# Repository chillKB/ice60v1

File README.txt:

This is my first ever PCB design. It is tested and working, but I was still learning and it definitely does not follow best practices.

Check out my GitHub profile for more recent designs since I love making PCBs, especially 60% ones.

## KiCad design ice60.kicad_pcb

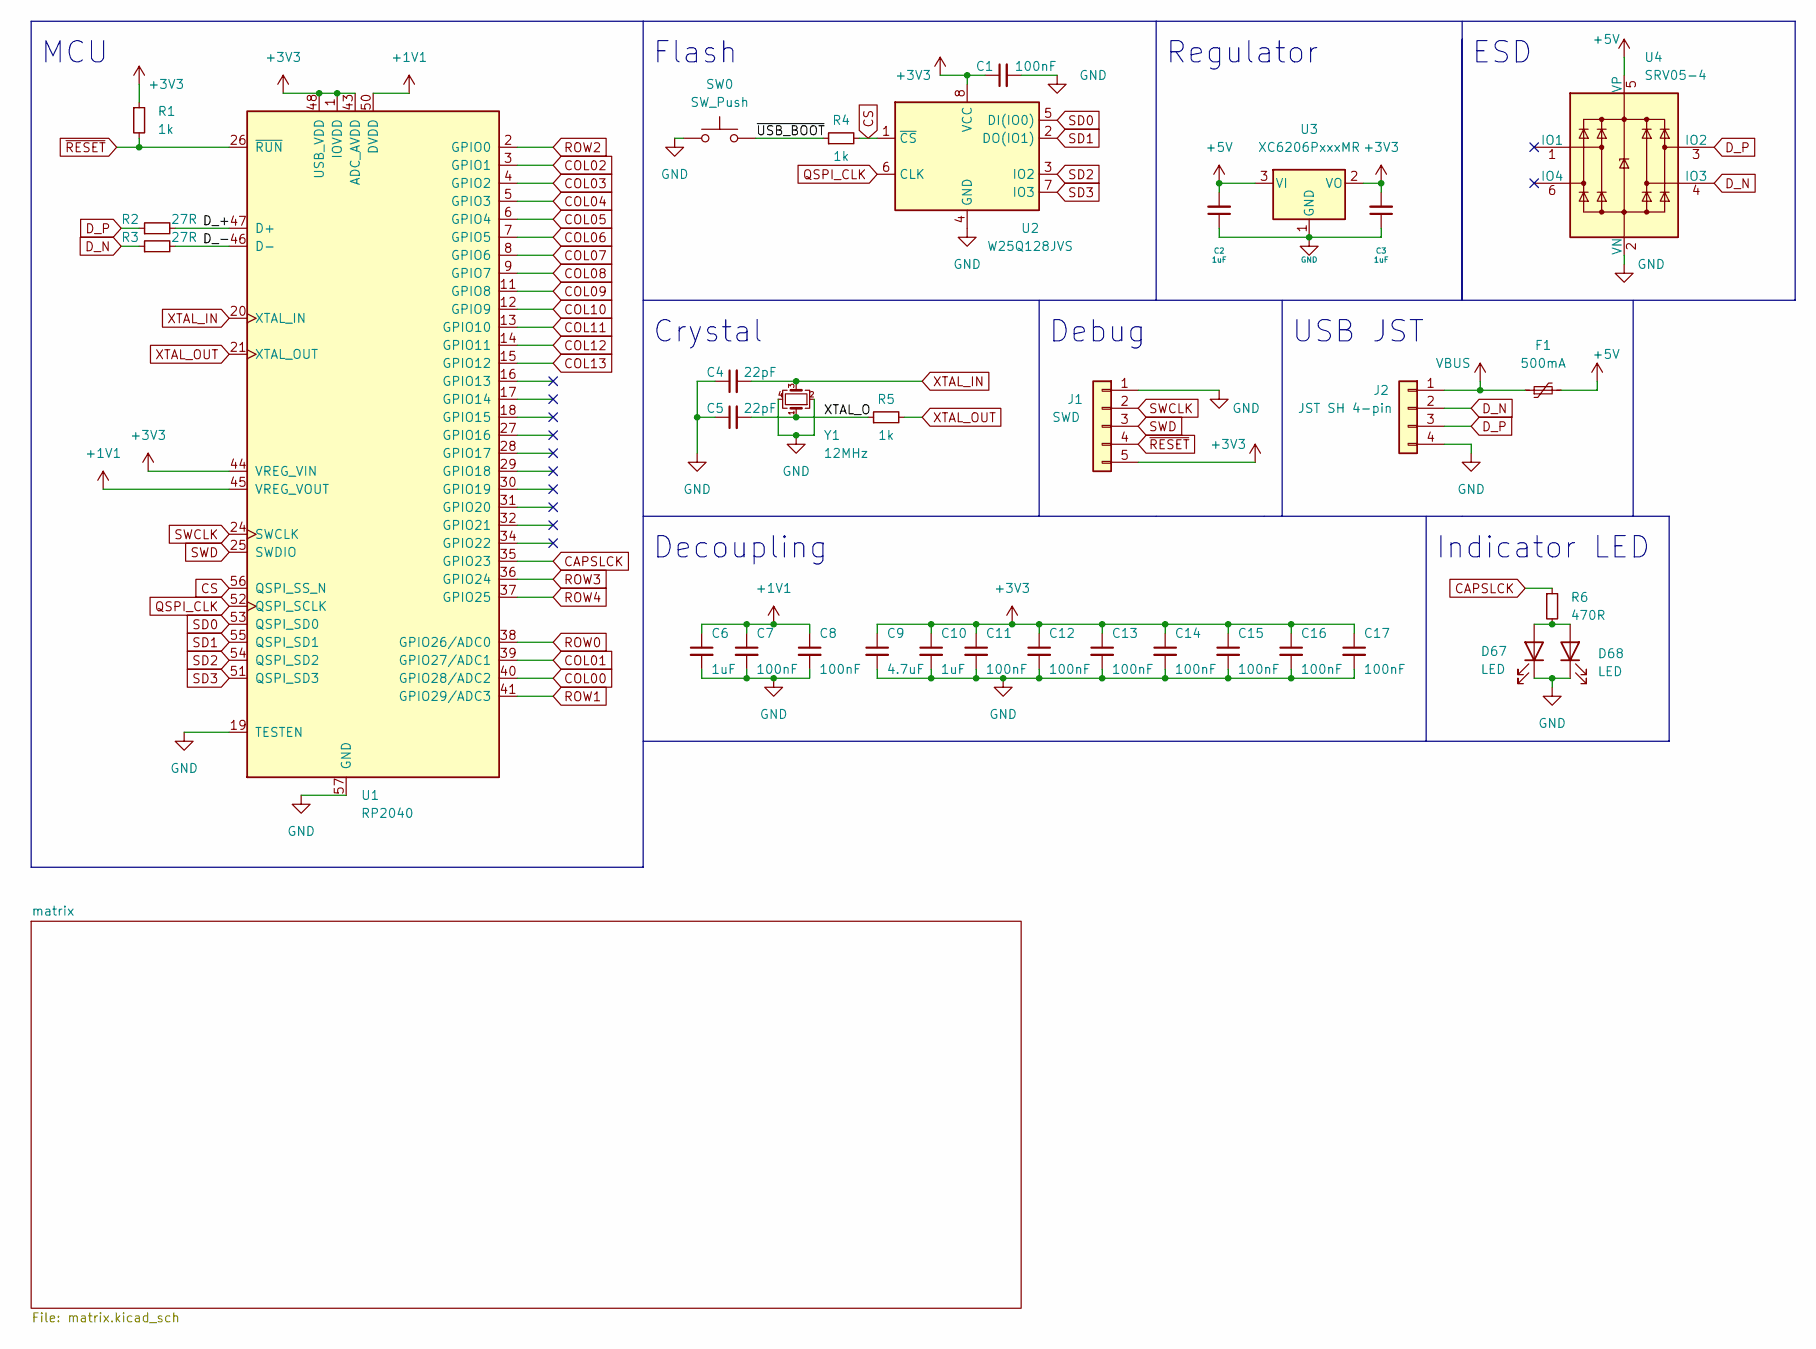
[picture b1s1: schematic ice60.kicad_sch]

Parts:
C1, C7, C8, C11, C12, C13, C14, C15, C16, C17: 100nF; C_0402_1005Metric; LCSC C1525
C2, C3, C6, C10: 1uF; C_0402_1005Metric; LCSC C52923
C4, C5: 22pF; C_0402_1005Metric; LCSC C1555
C9: 4.7uF; C_0402_1005Metric; LCSC C15525
D67: LED; LED_MX_3mm
D68: LED; LED_MX_3mm-FLIPPED
F1: 500mA; Fuse_1206_3216Metric; LCSC C135342
J1: SWD; PinSocket_1x05_P2.54mm_Vertical
J2: JST SH 4-pin; JST_SH_SM04B-SRSS-TB_1x04-1MP_P1.00mm_Horizontal; LCSC C160404
R1, R4, R5: 1k; R_0402_1005Metric; LCSC C11702
R2, R3: 27R; R_0603_1608Metric; LCSC C25190
R6: 470R; R_0402_1005Metric; LCSC C25117
SW0: SW_Push; PinSocket_1x02_P2.54mm_Vertical
U1: RP2040; RP2040-QFN-56; LCSC C2040
U2: W25Q128JVS; SOIC-8_5.23x5.23mm_P1.27mm; LCSC C131025
U3: XC6206PxxxMR; SOT-23; LCSC C5446
U4: SRV05-4; SOT-23-6-routable; LCSC C85364
Y1: 12MHz; Crystal_SMD_3225-4Pin_3.2x2.5mm; LCSC C9002

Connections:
+1V1: C6.1, C7.1, C8.1, U1.23 (DVDD), U1.45 (VREG_VOUT), U1.50 (DVDD)
+3V3: C1.1, C3.2, C9.1, C10.1, C11.1, C12.1, C13.1, C14.1, C15.1, C16.1, C17.1, J1.5, R1.1, U1.1 (IOVDD), U1.10 (IOVDD), U1.22 (IOVDD), U1.33 (IOVDD), U1.42 (IOVDD), U1.43 (ADC_AVDD), U1.44 (VREG_VIN), U1.48 (USB_VDD), U1.49 (IOVDD), U2.8 (VCC), U3.2 (VO)
+5V: C2.2, F1.2, U3.3 (VI), U4.5 (VP)
/D_+: R2.2, U1.47 (D+)
/D_-: R3.2, U1.46 (D-)
/XTAL_O: C5.2, R5.1, Y1.1
/~USB_BOOT: R4.1, SW0.2
CAPSLCK: R6.1, U1.35 (GPIO23)
COL00: U1.40 (GPIO28/ADC2); also elsewhere on the board
COL01: U1.39 (GPIO27/ADC1); also elsewhere on the board
COL02: U1.3 (GPIO1); also elsewhere on the board
COL03: U1.4 (GPIO2); also elsewhere on the board
COL04: U1.5 (GPIO3); also elsewhere on the board
COL05: U1.6 (GPIO4); also elsewhere on the board
COL06: U1.7 (GPIO5); also elsewhere on the board
COL07: U1.8 (GPIO6); also elsewhere on the board
COL08: U1.9 (GPIO7); also elsewhere on the board
COL09: U1.11 (GPIO8); also elsewhere on the board
COL10: U1.12 (GPIO9); also elsewhere on the board
COL11: U1.13 (GPIO10); also elsewhere on the board
COL12: U1.14 (GPIO11); also elsewhere on the board
COL13: U1.15 (GPIO12); also elsewhere on the board
CS: R4.2, U1.56 (QSPI_SS_N), U2.1 (~CS)
D_N: J2.2, R3.1, U4.4 (IO3)
D_P: J2.3, R2.1, U4.3 (IO2)
GND: C1.2, C2.1, C3.1, C4.1, C5.1, C6.2, C7.2, C8.2, C9.2, C10.2, C11.2, C12.2, C13.2, C14.2, C15.2, C16.2, C17.2, D67.1 (K), D68.1 (K), J1.1, J2.4, SW0.1, U1.19 (TESTEN), U1.57 (GND), U2.4 (GND), U3.1 (GND), U4.2 (VN), Y1.2, Y1.4
unnamed: D67.2 (A), D68.2 (A), R6.2
QSPI_CLK: U1.52 (QSPI_SCLK), U2.6 (CLK)
ROW0: U1.38 (GPIO26/ADC0); also elsewhere on the board
ROW1: U1.41 (GPIO29/ADC3); also elsewhere on the board
ROW2: U1.2 (GPIO0); also elsewhere on the board
ROW3: U1.36 (GPIO24); also elsewhere on the board
ROW4: U1.37 (GPIO25); also elsewhere on the board
SD0: U1.53 (QSPI_SD0), U2.5 (DI(IO0))
SD1: U1.55 (QSPI_SD1), U2.2 (DO(IO1))
SD2: U1.54 (QSPI_SD2), U2.3 (IO2)
SD3: U1.51 (QSPI_SD3), U2.7 (IO3)
SWCLK: J1.2, U1.24 (SWCLK)
SWD: J1.3, U1.25 (SWDIO)
VBUS: F1.1, J2.1
XTAL_IN: C4.2, U1.20 (XTAL_IN), Y1.3
XTAL_OUT: R5.2, U1.21 (XTAL_OUT)
~RESET: J1.4, R1.2, U1.26 (~RUN)

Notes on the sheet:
Crystal
Indicator LED
USB JST
Regulator
ESD
MCU
Debug
Flash
Decoupling

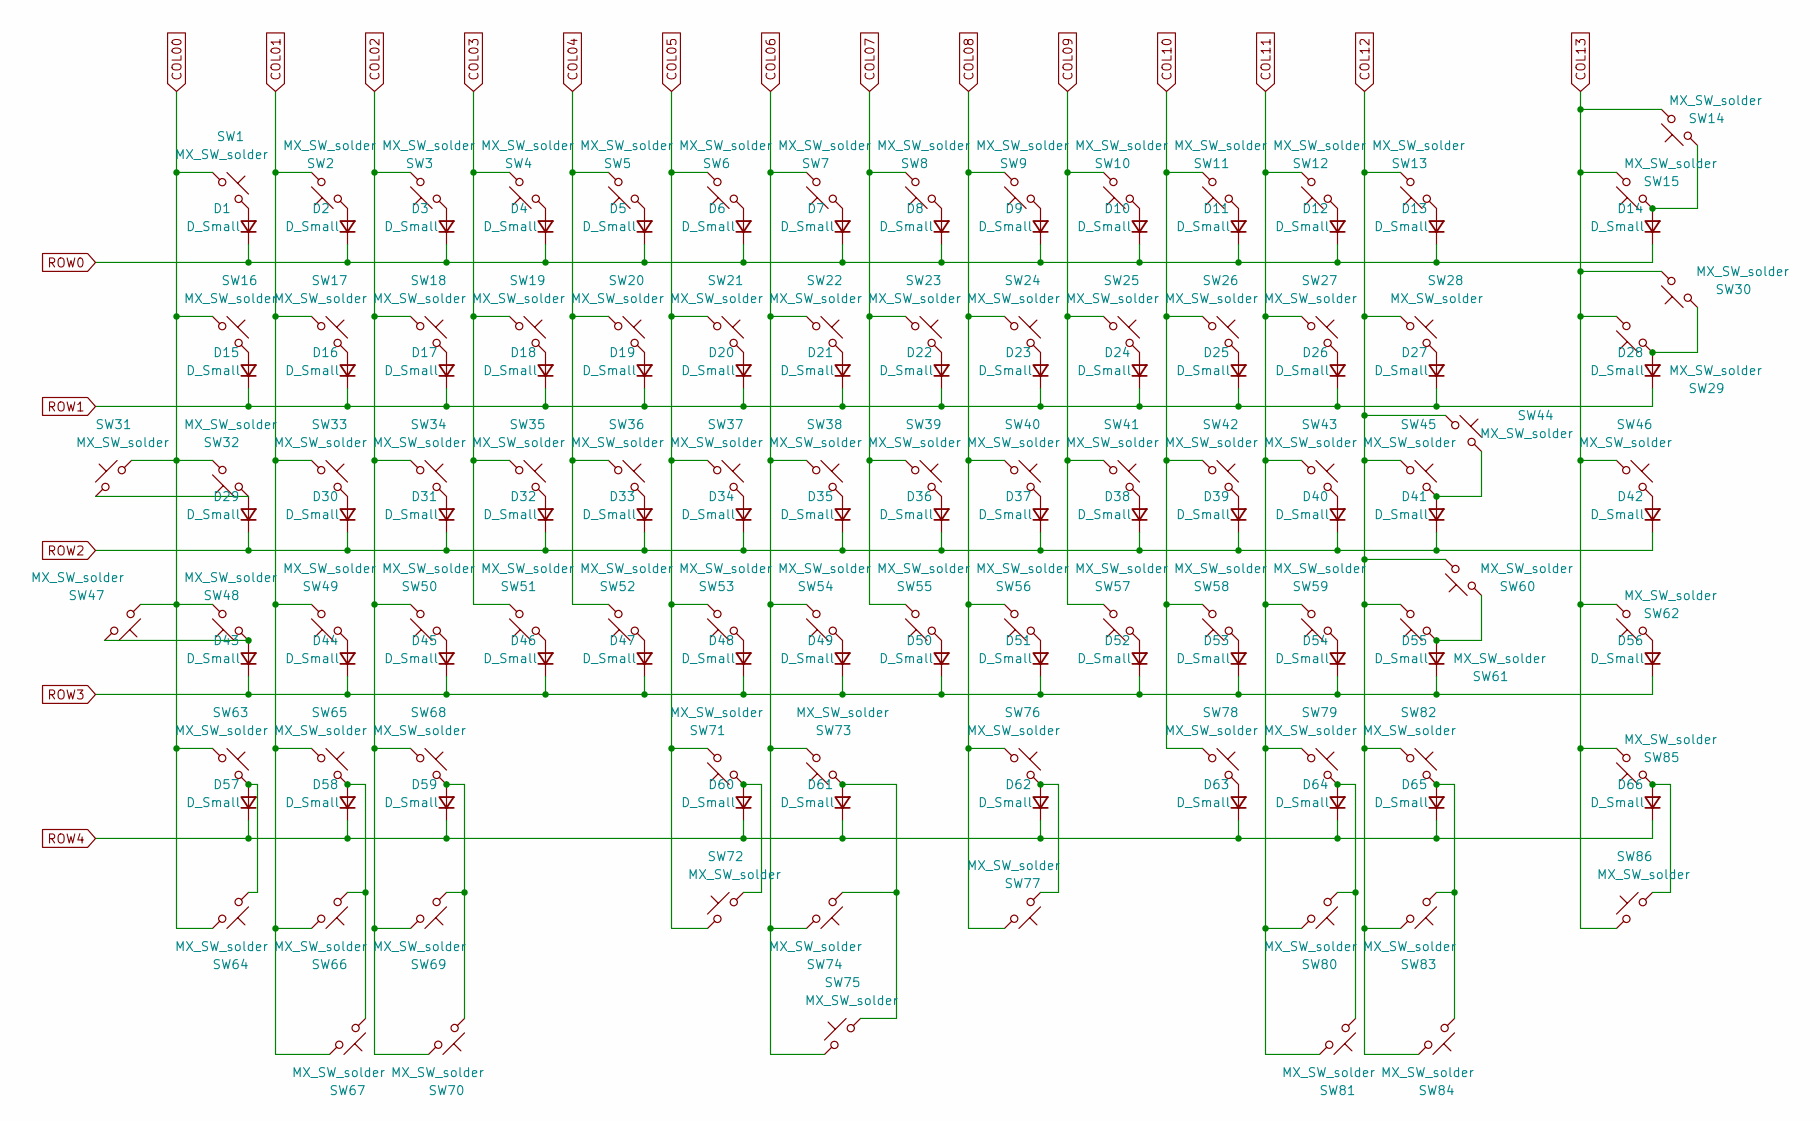
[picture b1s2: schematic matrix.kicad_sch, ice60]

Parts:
D1, D2, D3, D4, D5, D6, D7, D8, D9, D10, D11, D12, D13, D14, D15, D16, D17, D18, D19, D20, D21, D22, D23, D24, D25, D26, D27, D28, D29, D30, D31, D32, D33, D34, D35, D36, D37, D38, D39, D40, D41, D42, D43, D44, D45, D46, D47, D48, D49, D50, D51, D52, D53, D54, D55, D56, D57, D58, D59, D60, D61, D62, D63, D64, D65, D66: D_Small; D_SOD-123; LCSC C81598
SW1, SW2, SW3, SW4, SW5, SW6, SW7, SW8, SW9, SW10, SW11, SW12, SW13, SW14, SW15, SW17, SW18, SW19, SW20, SW21, SW22, SW23, SW24, SW25, SW26, SW27, SW28, SW30, SW33, SW34, SW35, SW36, SW37, SW38, SW39, SW40, SW41, SW42, SW43, SW44, SW45, SW46, SW48, SW49, SW50, SW51, SW52, SW53, SW54, SW55, SW56, SW57, SW58, SW59, SW61, SW62, SW66, SW71, SW72, SW73, SW75, SW76, SW77, SW83: MX_SW_solder; SW_MX_1u
SW16, SW29, SW64, SW69, SW80, SW86: MX_SW_solder; SW_MX_1.5u
SW31: MX_SW_solder; SW_MX_1.75u_stp
SW32, SW60: MX_SW_solder; SW_MX_1.75u
SW47, SW63, SW65, SW67, SW68, SW70, SW74, SW78, SW79, SW81, SW82, SW84, SW85: MX_SW_solder; SW_MX_1.25u

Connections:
COL00: SW1.1, SW16.1, SW31.1, SW32.2, SW47.2, SW48.2, SW63.1, SW64.1; also elsewhere on the board
COL01: SW2.2, SW17.1, SW33.1, SW49.2, SW65.1, SW66.1, SW67.1; also elsewhere on the board
COL02: SW3.2, SW18.1, SW34.1, SW50.2, SW68.1, SW69.1, SW70.1; also elsewhere on the board
COL03: SW4.2, SW19.1, SW35.1, SW51.2; also elsewhere on the board
COL04: SW5.2, SW20.1, SW36.1, SW52.2; also elsewhere on the board
COL05: SW6.2, SW21.1, SW37.1, SW53.2, SW71.2, SW72.2; also elsewhere on the board
COL06: SW7.2, SW22.1, SW38.1, SW54.2, SW73.2, SW74.1, SW75.2; also elsewhere on the board
COL07: SW8.2, SW23.1, SW39.1, SW55.2; also elsewhere on the board
COL08: SW9.2, SW24.1, SW40.1, SW56.2, SW76.1, SW77.1; also elsewhere on the board
COL09: SW10.2, SW25.1, SW41.1, SW57.2; also elsewhere on the board
COL10: SW11.2, SW26.1, SW42.1, SW58.2, SW78.1; also elsewhere on the board
COL11: SW12.2, SW27.1, SW43.1, SW59.2, SW79.1, SW80.1, SW81.1; also elsewhere on the board
COL12: SW13.2, SW28.1, SW44.1, SW45.1, SW60.2, SW61.2, SW82.1, SW83.1, SW84.1; also elsewhere on the board
COL13: SW14.2, SW15.2, SW29.2, SW30.2, SW46.1, SW62.2, SW85.2, SW86.2; also elsewhere on the board
unnamed: D1.2 (A), SW1.2
unnamed: D2.2 (A), SW2.1
unnamed: D3.2 (A), SW3.1
unnamed: D4.2 (A), SW4.1
unnamed: D5.2 (A), SW5.1
unnamed: D6.2 (A), SW6.1
unnamed: D7.2 (A), SW7.1
unnamed: D8.2 (A), SW8.1
unnamed: D9.2 (A), SW9.1
unnamed: D10.2 (A), SW10.1
unnamed: D11.2 (A), SW11.1
unnamed: D12.2 (A), SW12.1
unnamed: D13.2 (A), SW13.1
unnamed: D14.2 (A), SW14.1, SW15.1
unnamed: D15.2 (A), SW16.2
unnamed: D16.2 (A), SW17.2
unnamed: D17.2 (A), SW18.2
unnamed: D18.2 (A), SW19.2
unnamed: D19.2 (A), SW20.2
unnamed: D20.2 (A), SW21.2
unnamed: D21.2 (A), SW22.2
unnamed: D22.2 (A), SW23.2
unnamed: D23.2 (A), SW24.2
unnamed: D24.2 (A), SW25.2
unnamed: D25.2 (A), SW26.2
unnamed: D26.2 (A), SW27.2
unnamed: D27.2 (A), SW28.2
unnamed: D28.2 (A), SW29.1, SW30.1
unnamed: D29.2 (A), SW31.2, SW32.1
unnamed: D30.2 (A), SW33.2
unnamed: D31.2 (A), SW34.2
unnamed: D32.2 (A), SW35.2
unnamed: D33.2 (A), SW36.2
unnamed: D34.2 (A), SW37.2
unnamed: D35.2 (A), SW38.2
unnamed: D36.2 (A), SW39.2
unnamed: D37.2 (A), SW40.2
unnamed: D38.2 (A), SW41.2
unnamed: D39.2 (A), SW42.2
unnamed: D40.2 (A), SW43.2
unnamed: D41.2 (A), SW44.2, SW45.2
unnamed: D42.2 (A), SW46.2
unnamed: D43.2 (A), SW47.1, SW48.1
unnamed: D44.2 (A), SW49.1
unnamed: D45.2 (A), SW50.1
unnamed: D46.2 (A), SW51.1
unnamed: D47.2 (A), SW52.1
unnamed: D48.2 (A), SW53.1
unnamed: D49.2 (A), SW54.1
unnamed: D50.2 (A), SW55.1
unnamed: D51.2 (A), SW56.1
unnamed: D52.2 (A), SW57.1
unnamed: D53.2 (A), SW58.1
unnamed: D54.2 (A), SW59.1
unnamed: D55.2 (A), SW60.1, SW61.1
unnamed: D56.2 (A), SW62.1
unnamed: D57.2 (A), SW63.2, SW64.2
unnamed: D58.2 (A), SW65.2, SW66.2, SW67.2
unnamed: D59.2 (A), SW68.2, SW69.2, SW70.2
unnamed: D60.2 (A), SW71.1, SW72.1
unnamed: D61.2 (A), SW73.1, SW74.2, SW75.1
unnamed: D62.2 (A), SW76.2, SW77.2
unnamed: D63.2 (A), SW78.2
unnamed: D64.2 (A), SW79.2, SW80.2, SW81.2
unnamed: D65.2 (A), SW82.2, SW83.2, SW84.2
unnamed: D66.2 (A), SW85.1, SW86.1
ROW0: D1.1 (K), D2.1 (K), D3.1 (K), D4.1 (K), D5.1 (K), D6.1 (K), D7.1 (K), D8.1 (K), D9.1 (K), D10.1 (K), D11.1 (K), D12.1 (K), D13.1 (K), D14.1 (K); also elsewhere on the board
ROW1: D15.1 (K), D16.1 (K), D17.1 (K), D18.1 (K), D19.1 (K), D20.1 (K), D21.1 (K), D22.1 (K), D23.1 (K), D24.1 (K), D25.1 (K), D26.1 (K), D27.1 (K), D28.1 (K); also elsewhere on the board
ROW2: D29.1 (K), D30.1 (K), D31.1 (K), D32.1 (K), D33.1 (K), D34.1 (K), D35.1 (K), D36.1 (K), D37.1 (K), D38.1 (K), D39.1 (K), D40.1 (K), D41.1 (K), D42.1 (K); also elsewhere on the board
ROW3: D43.1 (K), D44.1 (K), D45.1 (K), D46.1 (K), D47.1 (K), D48.1 (K), D49.1 (K), D50.1 (K), D51.1 (K), D52.1 (K), D53.1 (K), D54.1 (K), D55.1 (K), D56.1 (K); also elsewhere on the board
ROW4: D57.1 (K), D58.1 (K), D59.1 (K), D60.1 (K), D61.1 (K), D62.1 (K), D63.1 (K), D64.1 (K), D65.1 (K), D66.1 (K); also elsewhere on the board

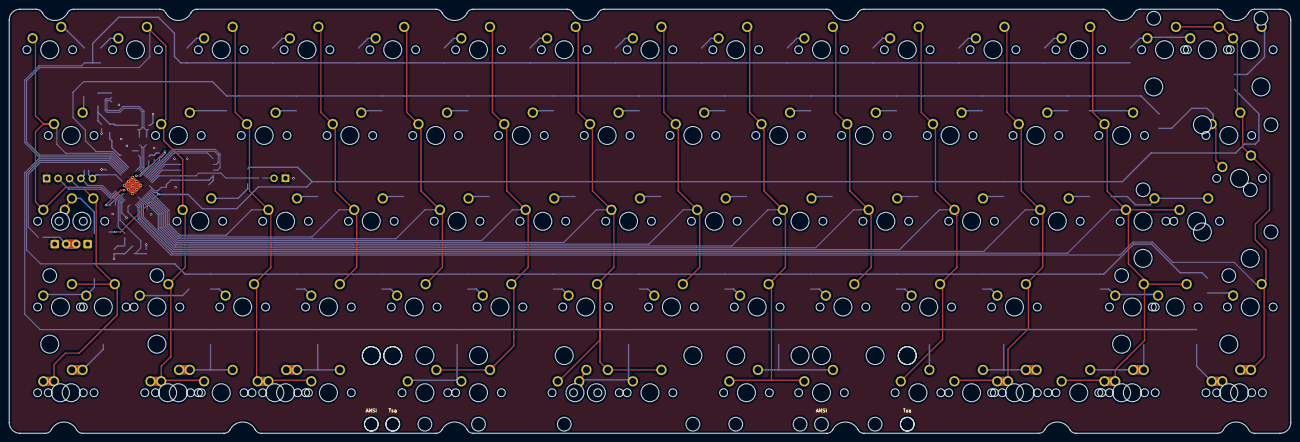
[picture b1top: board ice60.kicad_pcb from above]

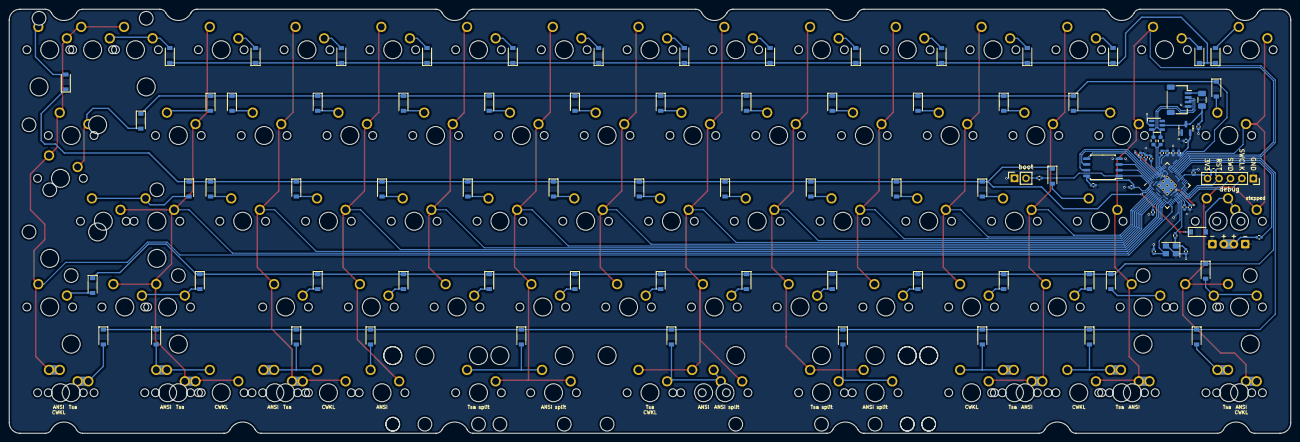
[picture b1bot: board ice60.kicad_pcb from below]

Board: 2 copper layers, 284.7 x 94.2 mm, 186 parts (98 on the bottom side), 109 nets.

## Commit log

2022-12-27 initial schematic w/o switch matrix
2022-12-27 update libraries
2022-12-27 remove old copies of libraries
2022-12-27 update files that slipped through library change
2022-12-27 relocate Sleep-lib license
2022-12-27 rearrange schematic
2022-12-27 initial matrix schematic
2022-12-28 clean up
2022-12-28 place switch and stab footprints
2022-12-28 flip some switches to simplify routing
2022-12-28 preliminary diode placement
2022-12-28 tweak diodes
2022-12-28 preliminary SMD component placements
2022-12-29 improve footprint positions
2022-12-29 wire up most things other than matrix
2022-12-29 route columns and row 0
2022-12-29 complete initial routing
2022-12-30 add ground fill and missing connections
2022-12-30 improve row3 and row4 routing
2022-12-30 o ring mounting cutouts
2022-12-31 tweaks
2023-01-01 redo vcc routing under MCU
2023-01-03 reroute USB data & several tweaks
2023-01-03 swap bulk cap & reroute debug
2023-01-03 add capslock in-switch LED indicator
2023-01-03 tweak JST placement
2023-01-04 add some layout indicators to silkscreen
2023-01-04 make JST placement less unique
2023-01-04 reroute crystal
2023-01-04 add part numbers for BOM
2023-01-08 add rounded tracks version and logo
2023-01-08 make one track a bit rounder
2023-01-08 please be the last tweak
2023-01-08 another track too close to a hole
2023-01-08 move some tracks slightly away from holes
2023-01-09 add secondary JST footprint (bakeneko)
2023-01-10 make iso enter west-facing
2023-01-10 exclude alternate JST from BOM and pos
2023-01-11 more tweaks
2023-01-11 update rounded version from latest unrounded
2023-01-11 adjust routing for C1
2023-01-11 ignore Production files and MacOS desktop services
2023-01-11 change output directory
2023-04-09 update to kicad 7, many small changes

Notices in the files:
ice60.kicad_sch:
© 2022 chillKB
CERN Open Hardware License version 2 -- Permissive
